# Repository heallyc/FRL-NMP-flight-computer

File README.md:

# FRL-NMP-flight-computer
2-layer KiCad flight computer PCB integrating Arduino Nano, MPU6050 IMU, BMP280 altimeter, and dual-servo control with regulated 3.3V power and isolated servo power.

Designed a 2-layer KiCad PCB integrating an Arduino Nano, MPU6050 IMU, BMP280 altimeter, and dual-servo control; designed 3.3V power regulation, I²C pull-ups, decoupling, ground planes, isolated servo power, and signal routing; completed ERC/DRC verification and generated fabrication files, BOM, schematic, and 3D renders.

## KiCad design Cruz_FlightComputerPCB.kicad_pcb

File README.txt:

README
Heally Cruz 10/31/2025
apparently i was supposed to do a 1x4 header for the sensors but then i wouldn't have an AD0 or SDO to attach to ground, so i just used the given components for the MPU6050 and BMP280 in kicad.

pin map
3V3 -> 3V3 pin
5V_USB -> +5V pin
GND -> GND pin
SDA (MPU6050) -> A4
SDI (BMP280) -> A4
SCK (BMP280) -> A5
SCL (MPU6050) -> A5
Servo signal D9 -> PWM_A (D9)
Servo signal D10 -> PWM_B (D10)
TP1(3V3) -> 3V3
TP2(GND) -> GND
TP3(SERVO_5V1) -> SERVO_5V
TP4(SDA1) -> SDA net
TP5(SCL1) -> SCL net
TP6(5V_USB1) -> +5V pin

power domains
5V_USB = 5V from Arduino Nano USB
SERVO_5V = 5V from external source attached to screw terminal
3V3 = 3.3V from Arduino Nano 
all grounds are common

i2c addresses used 
MPU6050 - AD0 (GND) : 0x68 
BMP280 - SDO (GND) : 0x76

servo header pinout
GND (pin 6)         | GND (pin 5)
SERVO_5V (pin 4)    | SERVO_5V (pin 3)
PWM_B (D10) (pin 2) | PWM_A (D9) (pin 1)

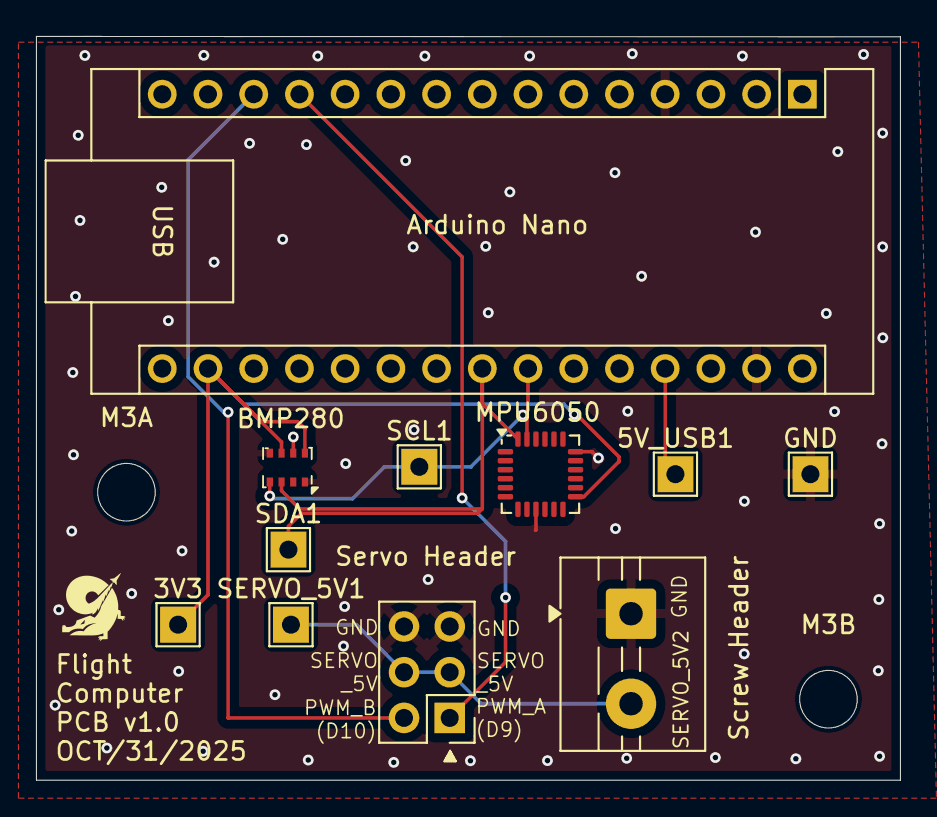
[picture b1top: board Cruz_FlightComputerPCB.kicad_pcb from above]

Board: 2 copper layers, 48.0 x 41.3 mm, 13 parts (0 on the bottom side), 8 nets.

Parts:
3V3, 5V_USB1: TestPoint; TestPoint_THTPad_2.0x2.0mm_Drill1.0mm
A1: Arduino_Nano_v3.x; Arduino_Nano
BMP280: BMP280; Bosch_LGA-8_2x2.5mm_P0.65mm_ClockwisePinNumbering
GND: TestPoint; TestPoint_THTPad_2.0x2.0mm_Drill1.0mm
J1: Conn_02x03; PinHeader_2x03_P2.54mm_Vertical
M3A, M3B: MountingHole; MountingHole_3.2mm_M3
MPU6050: MPU-6050; InvenSense_QFN-24_4x4mm_P0.5mm
SCL1: TestPoint; TestPoint_THTPad_2.0x2.0mm_Drill1.0mm
SDA1: TestPoint; TestPoint_THTPad_2.0x2.0mm_Drill1.0mm
SERVO_5V1: TestPoint; TestPoint_THTPad_2.0x2.0mm_Drill1.0mm
Screw Header: Screw_Terminal_01x02; TerminalBlock_MaiXu_MX126-5.0-02P_1x02_P5.00mm

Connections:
+3.3V: 3V3.1, A1.17 (3V3), BMP280.6 (VDDIO), BMP280.8 (VDD), MPU6050.13 (VDD)
+5V: 5V_USB1.1, A1.27 (+5V)
/PWM_A: A1.12 (D9), J1.1
/PWM_B: A1.13 (D10), J1.2
/SCL_3V3: A1.24 (A5), BMP280.4 (SCK), MPU6050.23 (SCL), SCL1.1
/SDA_3V3: A1.23 (A4), BMP280.3 (SDI), MPU6050.24 (SDA), SDA1.1
/SERVO 5V NET: J1.3, J1.4, SERVO_5V1.1, Screw Header.2
GND: A1.4 (GND), A1.29 (GND), BMP280.1 (GND), BMP280.5 (SDO), BMP280.7 (GND), GND.1, J1.5, J1.6, MPU6050.9 (AD0), MPU6050.18 (GND), Screw Header.1
